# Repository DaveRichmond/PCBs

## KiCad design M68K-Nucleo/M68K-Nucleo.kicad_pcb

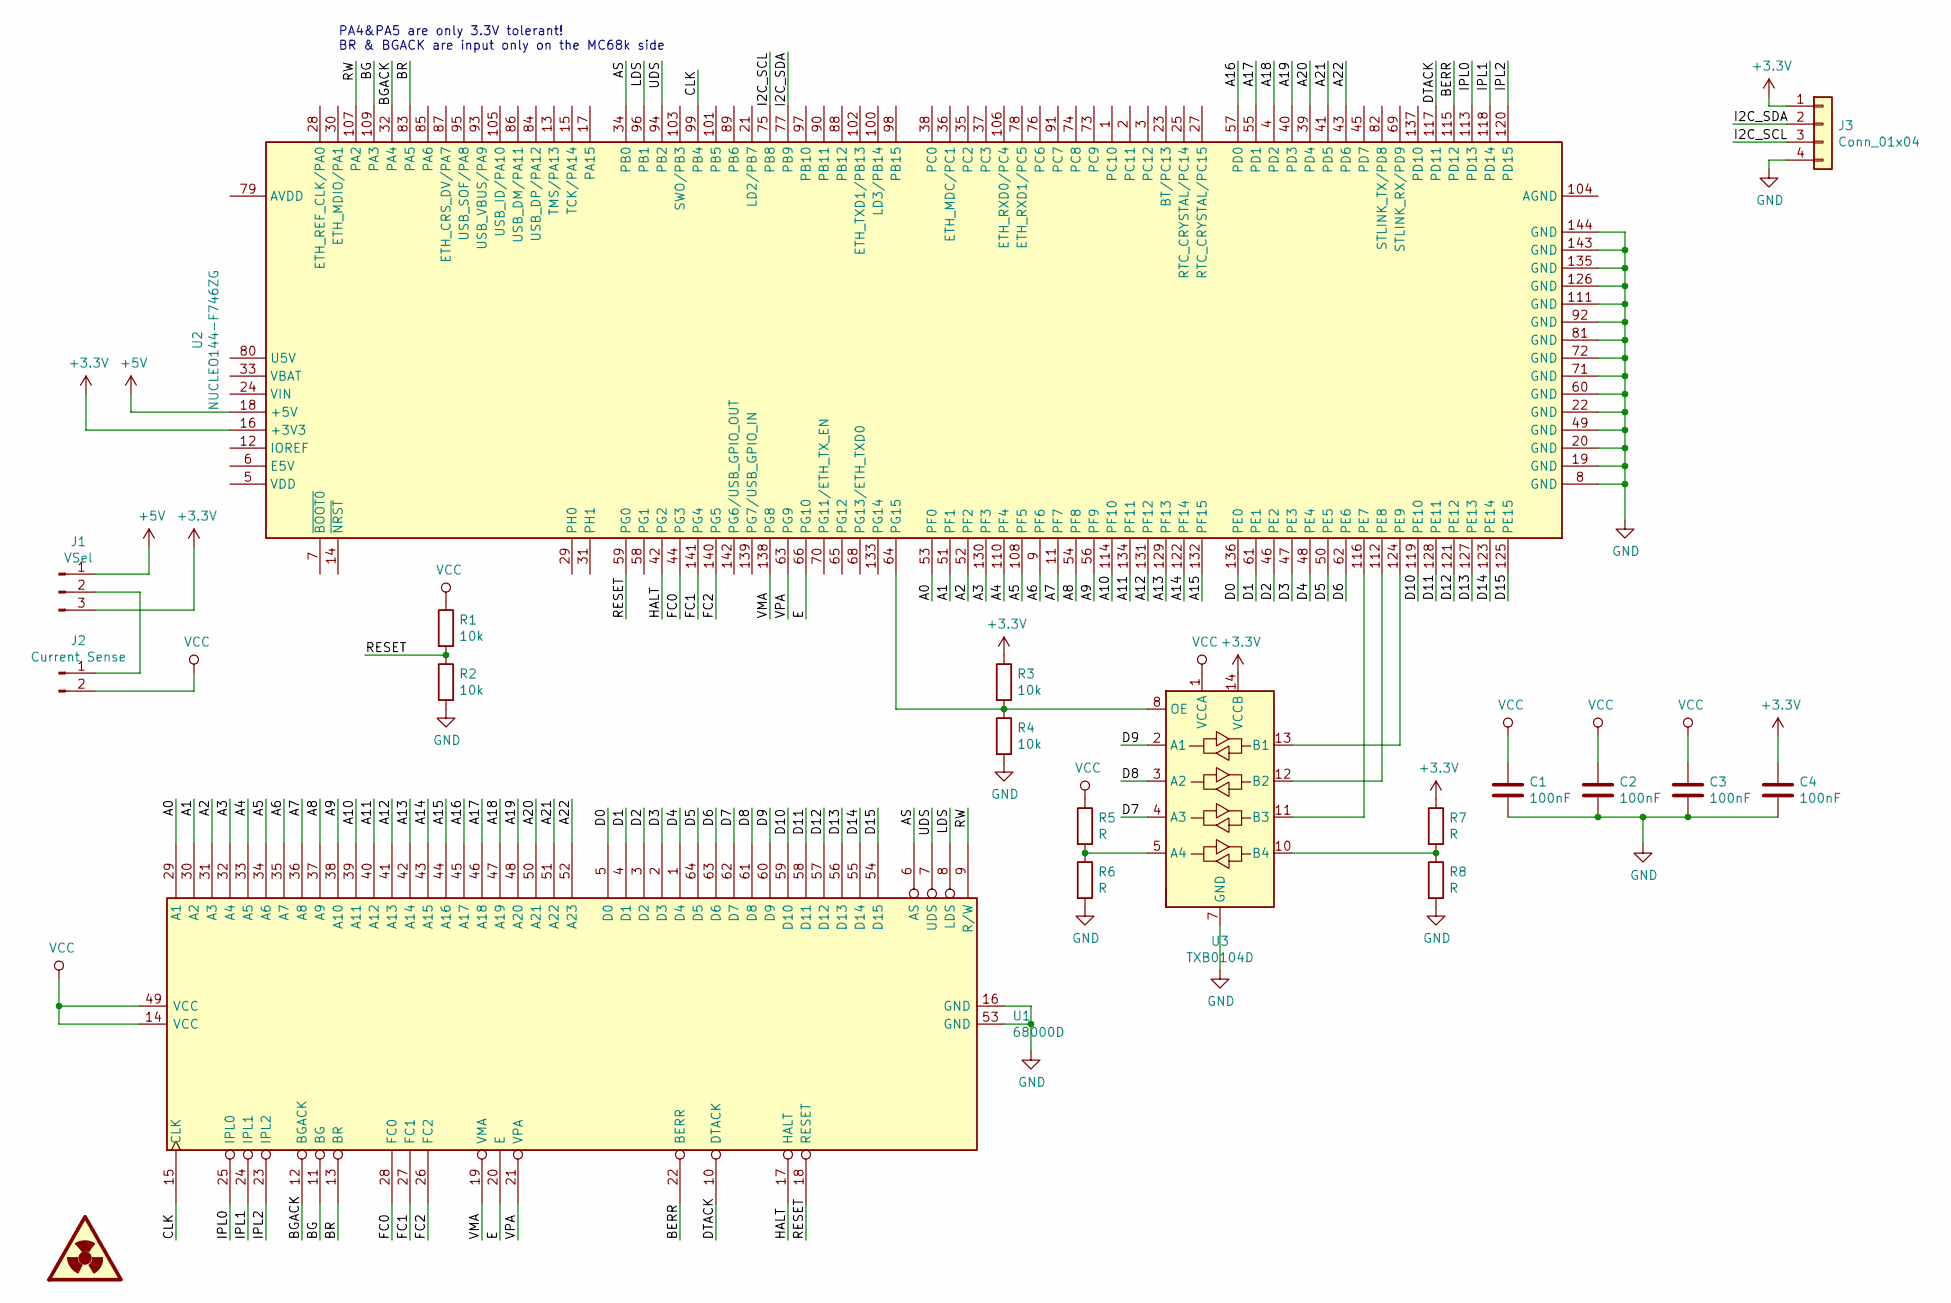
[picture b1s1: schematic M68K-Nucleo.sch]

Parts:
C1, C2, C3, C4: 100nF; C_1206_3216Metric
J1: VSel; PinHeader_1x03_P2.54mm_Vertical
J2: Current Sense; PinHeader_1x02_P2.54mm_Vertical
J3: Conn_01x04; PinHeader_1x04_P2.54mm_Vertical
R1, R2, R3, R4: 10k; R_1206_3216Metric
R5, R6, R7, R8: R; R_1206_3216Metric
U1: 68000D; DIP-64_W22.86mm_Socket_LongPads
U2: NUCLEO144-F746ZG; ST_Morpho_Connector_144_STLink
U3: TXB0104D; TSSOP-14_4.4x5mm_P0.65mm

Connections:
+3V3: C4.1, J1.3, J3.1, R3.1, R7.1, U2.16 (+3V3), U3.14 (VCCB)
+5V: J1.1, U2.18 (+5V)
/A0: U1.29 (A1), U2.53 (PF0)
/A1: U1.30 (A2), U2.51 (PF1)
/A2: U1.31 (A3), U2.52 (PF2)
/A3: U1.32 (A4), U2.130 (PF3)
/A4: U1.33 (A5), U2.110 (PF4)
/A5: U1.34 (A6), U2.108 (PF5)
/A6: U1.35 (A7), U2.9 (PF6)
/A7: U1.36 (A8), U2.11 (PF7)
/A8: U1.37 (A9), U2.54 (PF8)
/A9: U1.38 (A10), U2.56 (PF9)
/A10: U1.39 (A11), U2.114 (PF10)
/A11: U1.40 (A12), U2.134 (PF11)
/A12: U1.41 (A13), U2.131 (PF12)
/A13: U1.42 (A14), U2.129 (PF13)
/A14: U1.43 (A15), U2.122 (PF14)
/A15: U1.44 (A16), U2.132 (PF15)
/A16: U1.45 (A17), U2.57 (PD0)
/A17: U1.46 (A18), U2.55 (PD1)
/A18: U1.47 (A19), U2.4 (PD2)
/A19: U1.48 (A20), U2.40 (PD3)
/A20: U1.50 (A21), U2.39 (PD4)
/A21: U1.51 (A22), U2.41 (PD5)
/A22: U1.52 (A23), U2.43 (PD6)
/AS: U1.6 (AS), U2.34 (PB0)
/BERR: U1.22 (BERR), U2.115 (PD12)
/BG: U1.11 (BG), U2.109 (PA3)
/BGACK: U1.12 (BGACK), U2.32 (PA4)
/BR: U1.13 (BR), U2.83 (PA5)
/CLK: U1.15 (CLK), U2.99 (PB4)
/D0: U1.5 (D0), U2.136 (PE0)
/D1: U1.4 (D1), U2.61 (PE1)
/D2: U1.3 (D2), U2.46 (PE2)
/D3: U1.2 (D3), U2.47 (PE3)
/D4: U1.1 (D4), U2.48 (PE4)
/D5: U1.64 (D5), U2.50 (PE5)
/D6: U1.63 (D6), U2.62 (PE6)
/D7: U1.62 (D7), U3.4 (A3)
/D8: U1.61 (D8), U3.3 (A2)
/D9: U1.60 (D9), U3.2 (A1)
/D10: U1.59 (D10), U2.119 (PE10)
/D11: U1.58 (D11), U2.128 (PE11)
/D12: U1.57 (D12), U2.121 (PE12)
/D13: U1.56 (D13), U2.127 (PE13)
/D14: U1.55 (D14), U2.123 (PE14)
/D15: U1.54 (D15), U2.125 (PE15)
/DTACK: U1.10 (DTACK), U2.117 (PD11)
/E: U1.20 (E), U2.66 (PG10)
/FC0: U1.28 (FC0), U2.44 (PG3)
/FC1: U1.27 (FC1), U2.141 (PG4)
/FC2: U1.26 (FC2), U2.140 (PG5)
/HALT: U1.17 (HALT), U2.42 (PG2)
/I2C_SCL: J3.3, U2.75 (PB8)
/I2C_SDA: J3.2, U2.77 (PB9)
/IPL0: U1.25 (IPL0), U2.113 (PD13)
/IPL1: U1.24 (IPL1), U2.118 (PD14)
/IPL2: U1.23 (IPL2), U2.120 (PD15)
/LDS: U1.8 (LDS), U2.96 (PB1)
/RESET: R1.2, R2.1, U1.18 (RESET), U2.59 (PG0)
/RW: U1.9 (R/W), U2.107 (PA2)
/UDS: U1.7 (UDS), U2.94 (PB2)
/VMA: U1.19 (VMA), U2.138 (PG8)
/VPA: U1.21 (VPA), U2.63 (PG9)
GND: C1.2, C2.2, C3.2, C4.2, J3.4, R2.2, R4.2, R6.2, R8.2, U1.16 (GND), U1.53 (GND), U2.8 (GND), U2.19 (GND), U2.20 (GND), U2.22 (GND), U2.49 (GND), U2.60 (GND), U2.71 (GND), U2.72 (GND), U2.81 (GND), U2.92 (GND), U2.111 (GND), U2.126 (GND), U2.135 (GND), U2.143 (GND), U2.144 (GND), U3.7 (GND)
unnamed: J1.2, J2.1
unnamed: R3.2, R4.1, U2.64 (PG15), U3.8 (OE)
unnamed: R5.2, R6.1, U3.5 (A4)
unnamed: R7.2, R8.1, U3.10 (B4)
unnamed: U2.112 (PE8), U3.12 (B2)
unnamed: U2.116 (PE7), U3.11 (B3)
unnamed: U2.124 (PE9), U3.13 (B1)
VCC: C1.1, C2.1, C3.1, J2.2, R1.1, R5.1, U1.14 (VCC), U1.49 (VCC), U3.1 (VCCA)

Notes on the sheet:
PA4&PA5 are only 3.3V tolerant! BR & BGACK are input only on the MC68k side

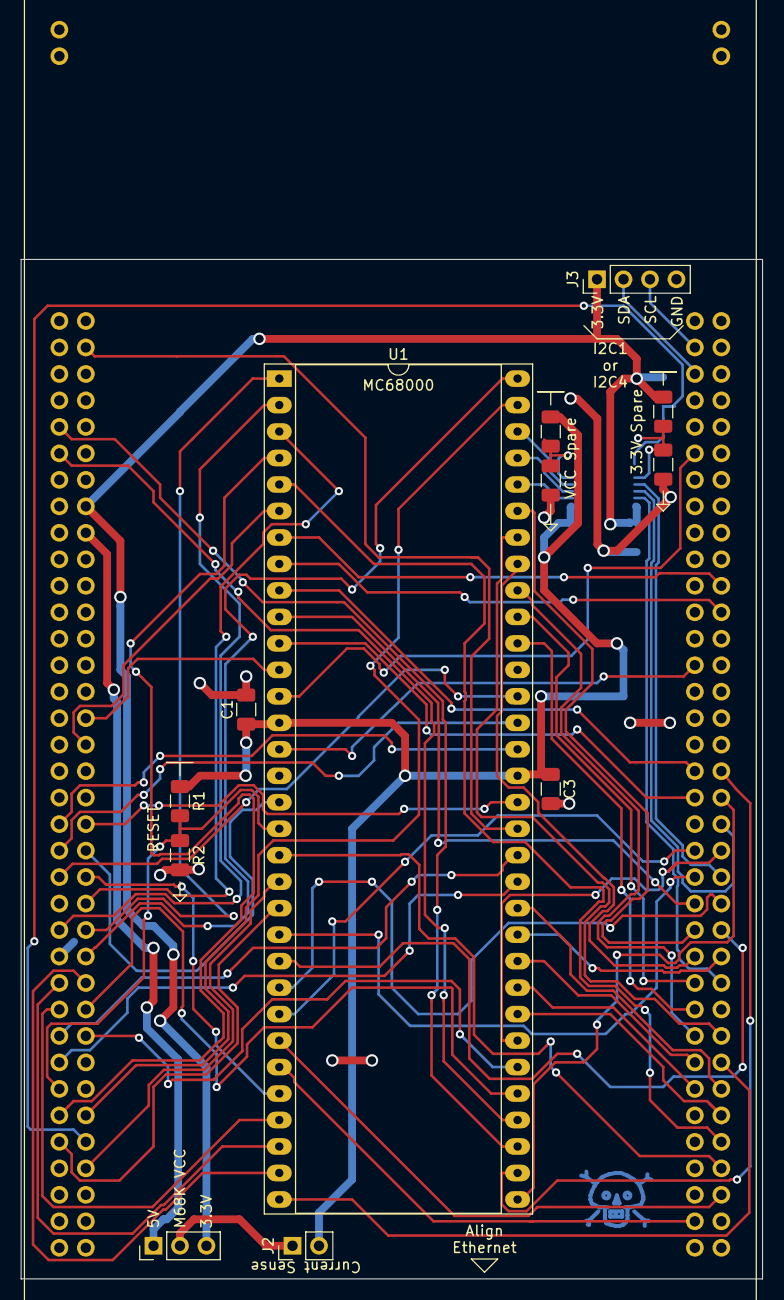
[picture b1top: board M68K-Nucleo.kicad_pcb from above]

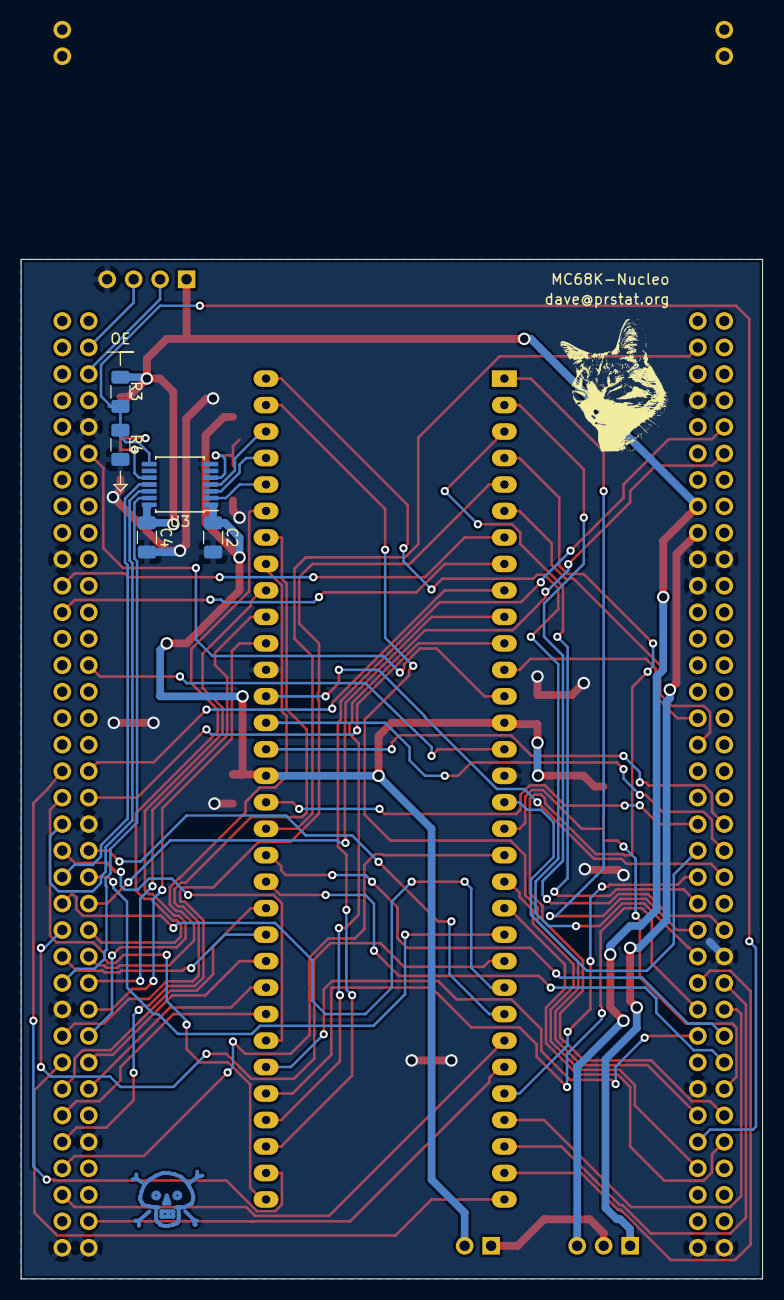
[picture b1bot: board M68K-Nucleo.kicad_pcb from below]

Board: 2 copper layers, 71.1 x 97.8 mm, 18 parts (5 on the bottom side), 73 nets.

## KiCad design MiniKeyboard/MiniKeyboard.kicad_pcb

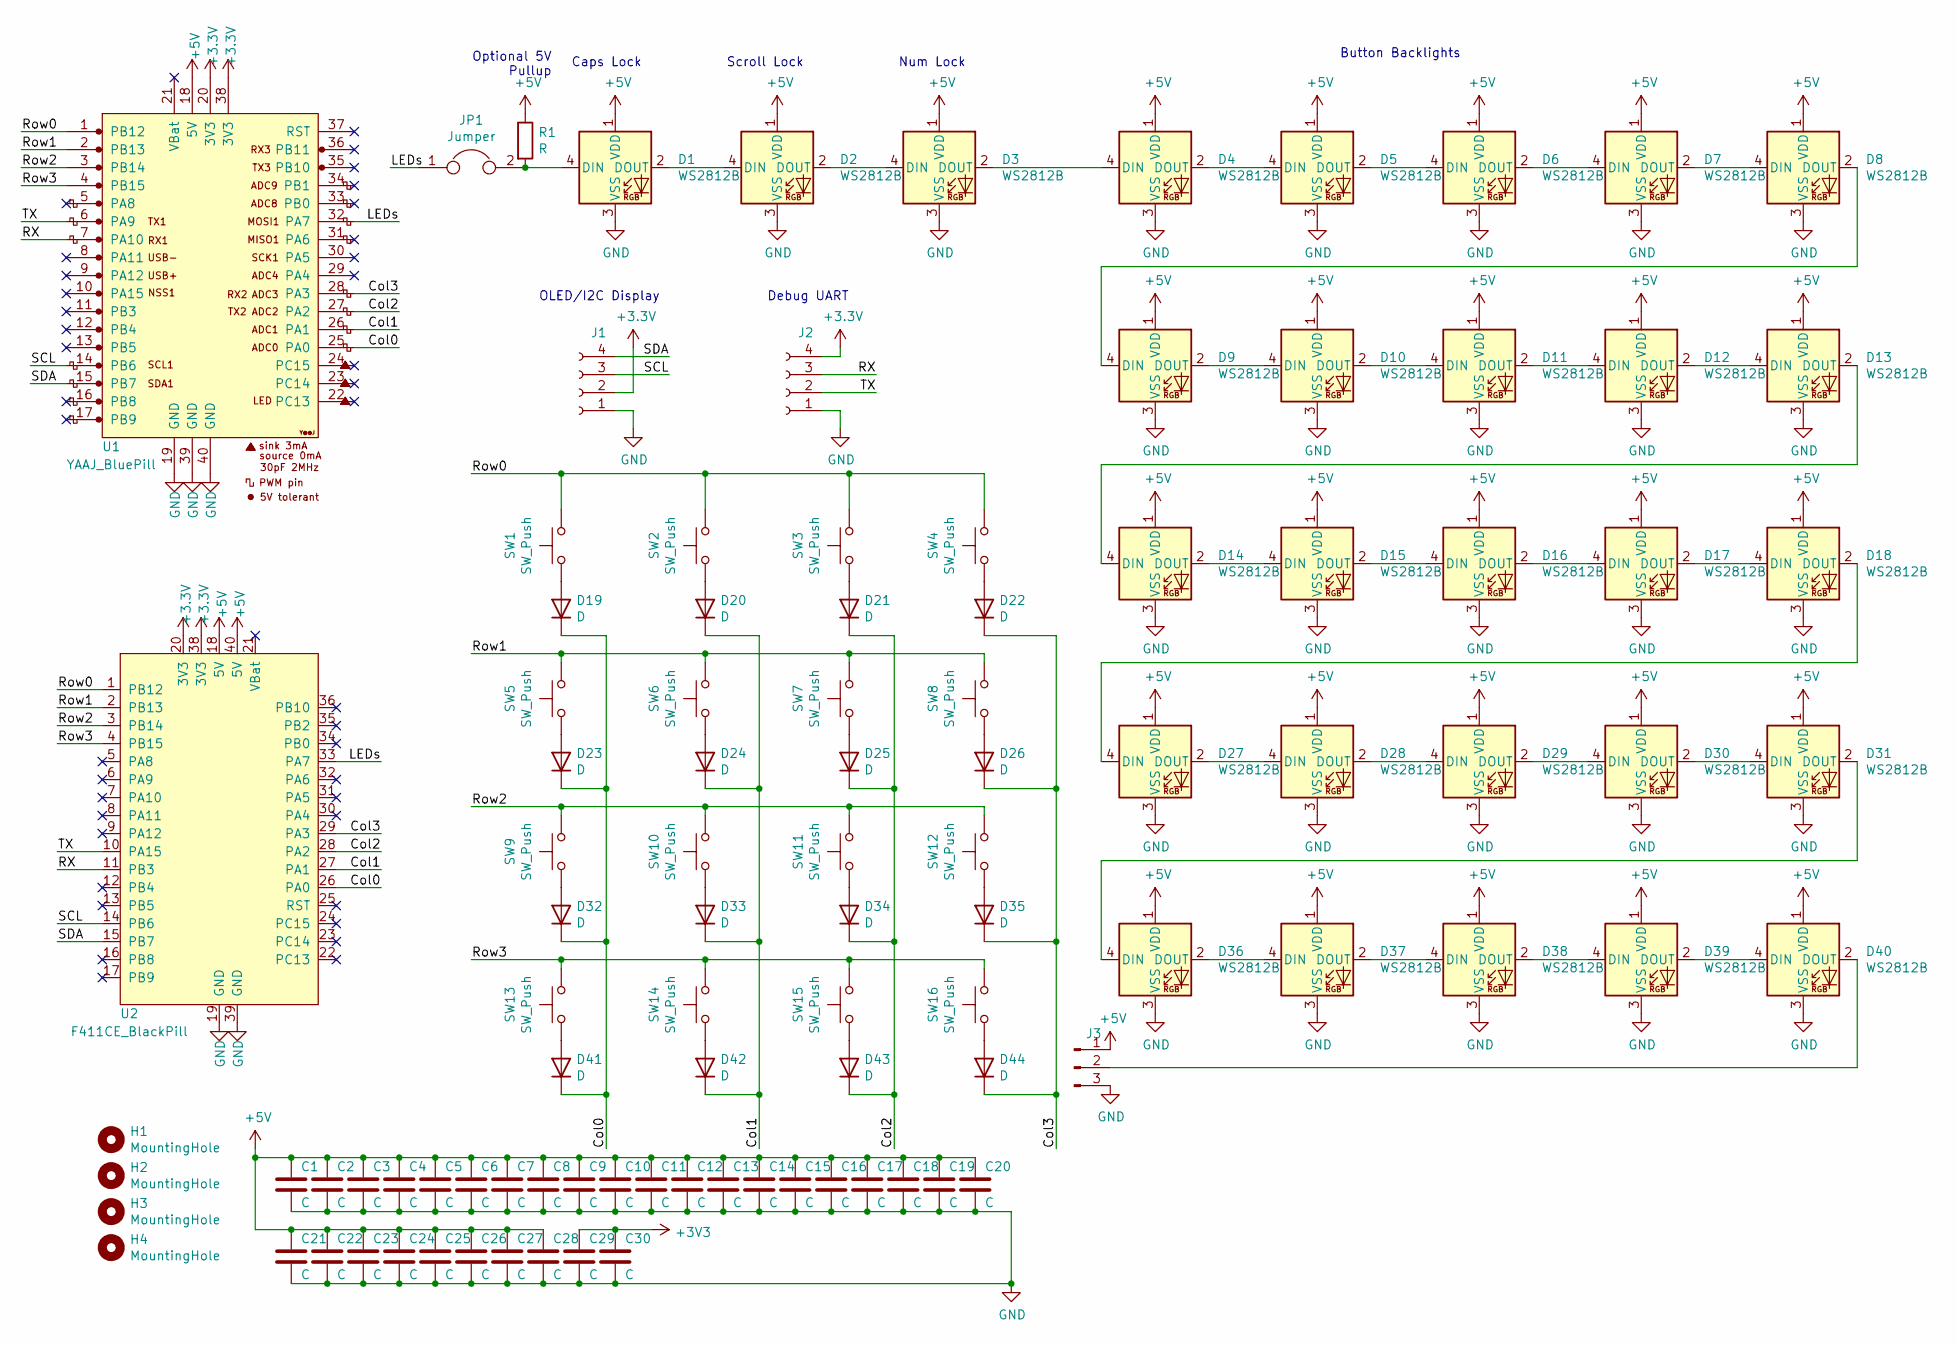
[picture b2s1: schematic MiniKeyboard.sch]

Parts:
C1, C2, C3, C4, C5, C6, C7, C8, C9, C10, C11, C12, C13, C14, C15, C16, C17, C18, C19, C20, C21, C22, C23, C24, C25, C26, C27, C28, C29, C30: C; C_0805_2012Metric_Pad1.18x1.45mm_HandSolder
D1, D2, D3, D4, D5, D6, D7, D8, D9, D10, D11, D12, D13, D14, D15, D16, D17, D18, D27, D28, D29, D30, D31, D36, D37, D38, D39, D40: WS2812B; LED_WS2812B_PLCC4_5.0x5.0mm_P3.2mm
D19, D20, D21, D22, D23, D24, D25, D26, D32, D33, D34, D35, D41, D42, D43, D44: D; D_SOT-23_ANK
H1, H2, H3, H4: MountingHole; MountingHole_5mm
J1, J2: Conn_01x04_Female; PinSocket_1x04_P2.54mm_Vertical
J3: Conn_01x03_Male; PinSocket_1x03_P2.54mm_Vertical
JP1: Jumper; SolderJumper-2_P1.3mm_Bridged_RoundedPad1.0x1.5mm
R1: R; R_1206_3216Metric_Pad1.30x1.75mm_HandSolder
SW1, SW2, SW3, SW4, SW5, SW6, SW7, SW8, SW9, SW10, SW11, SW12, SW13, SW14, SW15, SW16: SW_Push; SW_Cherry_MX_1.00u_PCB
U1: YAAJ_BluePill; YAAJ_BluePill_2
U2: F411CE_BlackPill; F411CE-Blackpill

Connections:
+5V: C1.1, C2.1, C3.1, C4.1, C5.1, C6.1, C7.1, C8.1, C9.1, C10.1, C11.1, C12.1, C13.1, C14.1, C15.1, C16.1, C17.1, C18.1, C19.1, C20.1, C21.1, C22.1, C23.1, C24.1, C25.1, C26.1, C27.1, C28.1, D1.1 (VDD), D2.1 (VDD), D3.1 (VDD), D4.1 (VDD), D5.1 (VDD), D6.1 (VDD), D7.1 (VDD), D8.1 (VDD), D9.1 (VDD), D10.1 (VDD), D11.1 (VDD), D12.1 (VDD), D13.1 (VDD), D14.1 (VDD), D15.1 (VDD), D16.1 (VDD), D17.1 (VDD), D18.1 (VDD), D27.1 (VDD), D28.1 (VDD), D29.1 (VDD), D30.1 (VDD), D31.1 (VDD), D36.1 (VDD), D37.1 (VDD), D38.1 (VDD), D39.1 (VDD), D40.1 (VDD), J3.1, R1.1, U1.18 (5V), U2.18 (5V), U2.40 (5V)
/Col0: D19.1 (K), D23.1 (K), D32.1 (K), D41.1 (K), U1.25 (PA0), U2.26 (PA0)
/Col1: D20.1 (K), D24.1 (K), D33.1 (K), D42.1 (K), U1.26 (PA1), U2.27 (PA1)
/Col2: D21.1 (K), D25.1 (K), D34.1 (K), D43.1 (K), U1.27 (PA2), U2.28 (PA2)
/Col3: D22.1 (K), D26.1 (K), D35.1 (K), D44.1 (K), U1.28 (PA3), U2.29 (PA3)
/LEDs: JP1.1, U1.32 (PA7), U2.33 (PA7)
/RX: J2.3, U1.7 (PA10), U2.11 (PB3)
/Row0: SW1.2, SW2.2, SW3.2, SW4.2, U1.1 (PB12), U2.1 (PB12)
/Row1: SW5.2, SW6.2, SW7.2, SW8.2, U1.2 (PB13), U2.2 (PB13)
/Row2: SW9.2, SW10.2, SW11.2, SW12.2, U1.3 (PB14), U2.3 (PB14)
/Row3: SW13.2, SW14.2, SW15.2, SW16.2, U1.4 (PB15), U2.4 (PB15)
/SCL: J1.3, U1.14 (PB6), U2.14 (PB6)
/SDA: J1.4, U1.15 (PB7), U2.15 (PB7)
/TX: J2.2, U1.6 (PA9), U2.10 (PA15)
GND: C1.2, C2.2, C3.2, C4.2, C5.2, C6.2, C7.2, C8.2, C9.2, C10.2, C11.2, C12.2, C13.2, C14.2, C15.2, C16.2, C17.2, C18.2, C19.2, C20.2, C21.2, C22.2, C23.2, C24.2, C25.2, C26.2, C27.2, C28.2, C29.2, C30.2, D1.3 (VSS), D2.3 (VSS), D3.3 (VSS), D4.3 (VSS), D5.3 (VSS), D6.3 (VSS), D7.3 (VSS), D8.3 (VSS), D9.3 (VSS), D10.3 (VSS), D11.3 (VSS), D12.3 (VSS), D13.3 (VSS), D14.3 (VSS), D15.3 (VSS), D16.3 (VSS), D17.3 (VSS), D18.3 (VSS), D27.3 (VSS), D28.3 (VSS), D29.3 (VSS), D30.3 (VSS), D31.3 (VSS), D36.3 (VSS), D37.3 (VSS), D38.3 (VSS), D39.3 (VSS), D40.3 (VSS), J1.1, J2.1, J3.3, U1.19 (GND), U1.39 (GND), U1.40 (GND), U2.19 (GND), U2.39 (GND)
unnamed: D1.2 (DOUT), D2.4 (DIN)
unnamed: D1.4 (DIN), JP1.2, R1.2
unnamed: D2.2 (DOUT), D3.4 (DIN)
unnamed: D3.2 (DOUT), D4.4 (DIN)
unnamed: D4.2 (DOUT), D5.4 (DIN)
unnamed: D5.2 (DOUT), D6.4 (DIN)
unnamed: D6.2 (DOUT), D7.4 (DIN)
unnamed: D7.2 (DOUT), D8.4 (DIN)
unnamed: D8.2 (DOUT), D9.4 (DIN)
unnamed: D10.2 (DOUT), D11.4 (DIN)
unnamed: D9.2 (DOUT), D10.4 (DIN)
unnamed: D11.2 (DOUT), D12.4 (DIN)
unnamed: D12.2 (DOUT), D13.4 (DIN)
unnamed: D13.2 (DOUT), D14.4 (DIN)
unnamed: D14.2 (DOUT), D15.4 (DIN)
unnamed: D15.2 (DOUT), D16.4 (DIN)
unnamed: D16.2 (DOUT), D17.4 (DIN)
unnamed: D17.2 (DOUT), D18.4 (DIN)
unnamed: D18.2 (DOUT), D27.4 (DIN)
unnamed: D19.2 (A), SW1.1
unnamed: D20.2 (A), SW2.1
unnamed: D21.2 (A), SW3.1
unnamed: D22.2 (A), SW4.1
unnamed: D23.2 (A), SW5.1
unnamed: D24.2 (A), SW6.1
unnamed: D25.2 (A), SW7.1
unnamed: D26.2 (A), SW8.1
unnamed: D27.2 (DOUT), D28.4 (DIN)
unnamed: D28.2 (DOUT), D29.4 (DIN)
unnamed: D29.2 (DOUT), D30.4 (DIN)
unnamed: D30.2 (DOUT), D31.4 (DIN)
unnamed: D31.2 (DOUT), D36.4 (DIN)
unnamed: D32.2 (A), SW9.1
unnamed: D33.2 (A), SW10.1
unnamed: D34.2 (A), SW11.1
unnamed: D35.2 (A), SW12.1
unnamed: D36.2 (DOUT), D37.4 (DIN)
unnamed: D37.2 (DOUT), D38.4 (DIN)
unnamed: D38.2 (DOUT), D39.4 (DIN)
unnamed: D39.2 (DOUT), D40.4 (DIN)
unnamed: D40.2 (DOUT), J3.2
unnamed: D41.2 (A), SW13.1
unnamed: D42.2 (A), SW14.1
unnamed: D43.2 (A), SW15.1
unnamed: D44.2 (A), SW16.1

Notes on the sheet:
OLED/I2C Display
Debug UART
Caps Lock
Scroll Lock
Num Lock
Button Backlights
Optional 5V Pullup

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
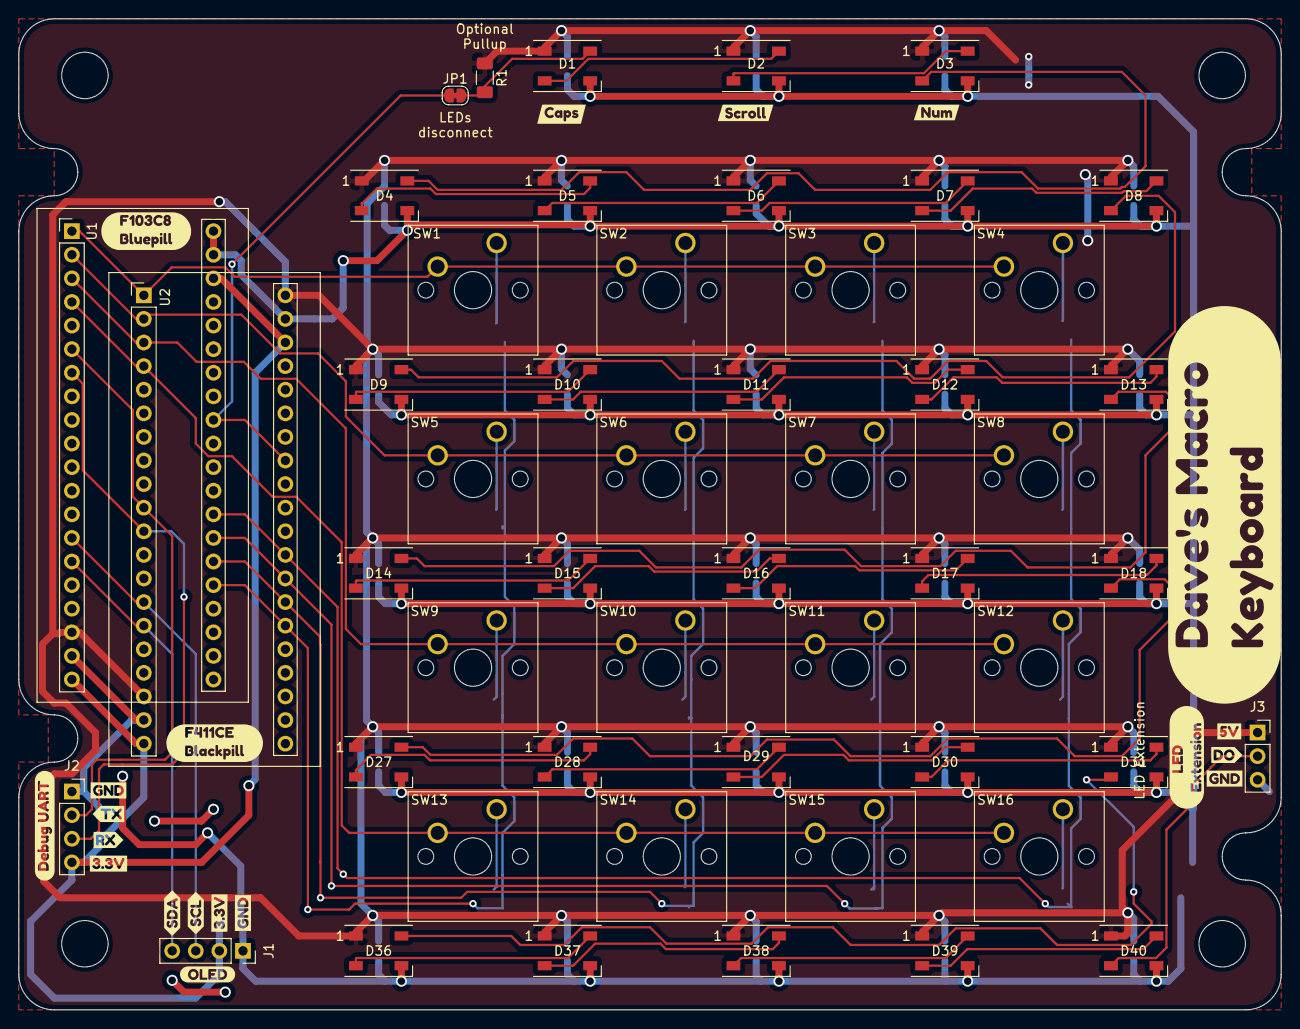
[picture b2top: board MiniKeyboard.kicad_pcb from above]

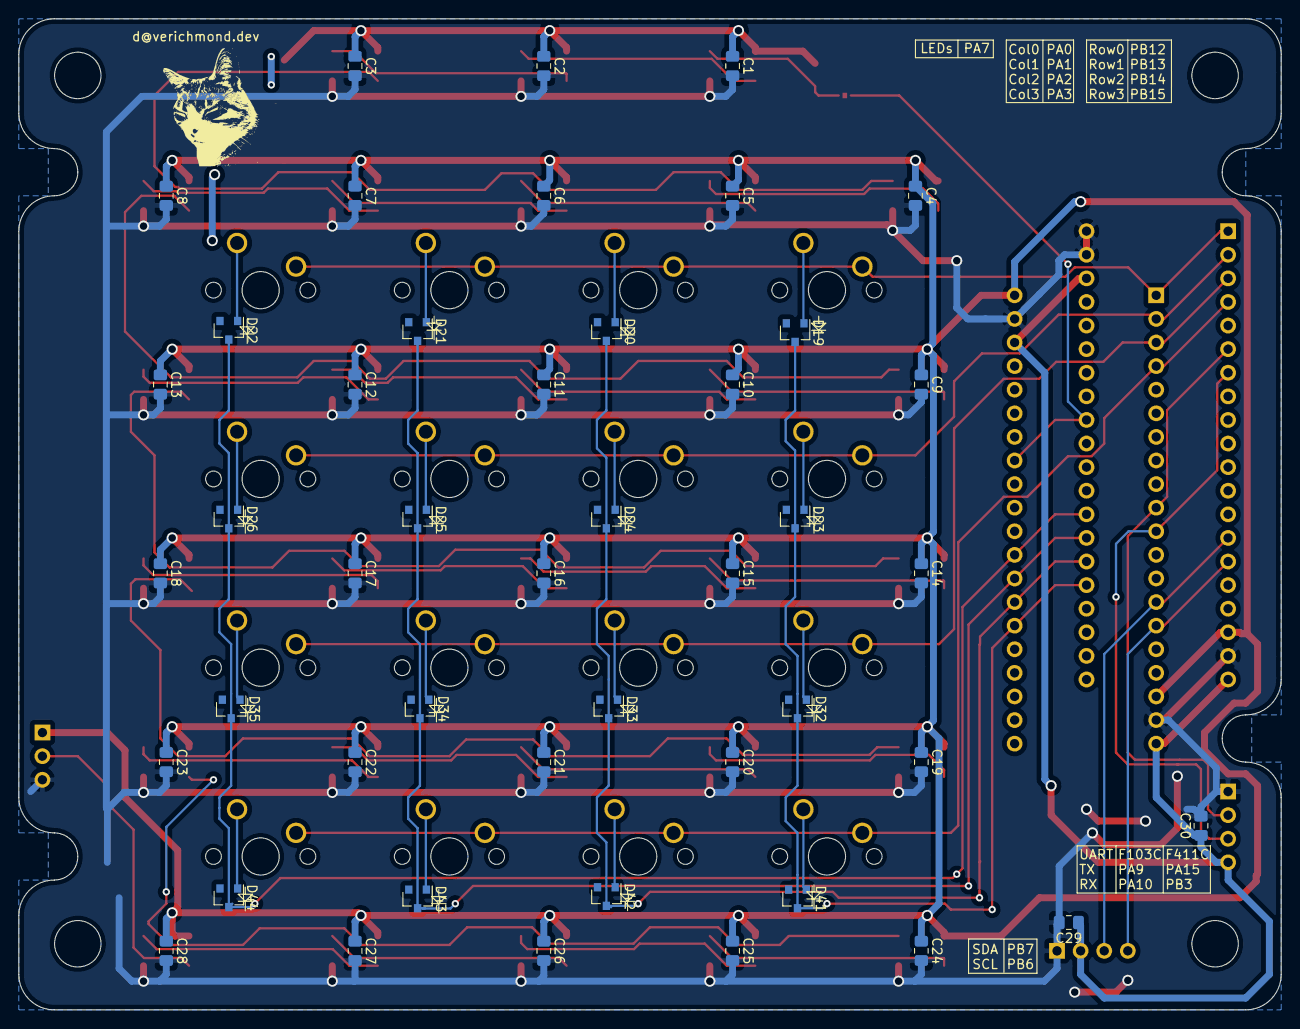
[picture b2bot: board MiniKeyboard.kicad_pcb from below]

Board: 2 copper layers, 135.9 x 106.7 mm, 121 parts (46 on the bottom side), 61 nets.

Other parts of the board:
svg2mod, svg2mod#2, svg2mod#3, svg2mod#4, svg2mod#5, svg2mod#6, svg2mod#7, svg2mod#8, svg2mod#9, svg2mod#10, svg2mod#11, svg2mod#12, svg2mod#13, svg2mod#14, svg2mod#15, svg2mod#16, svg2mod#17, svg2mod#18, svg2mod#19, svg2mod#20: G***; label

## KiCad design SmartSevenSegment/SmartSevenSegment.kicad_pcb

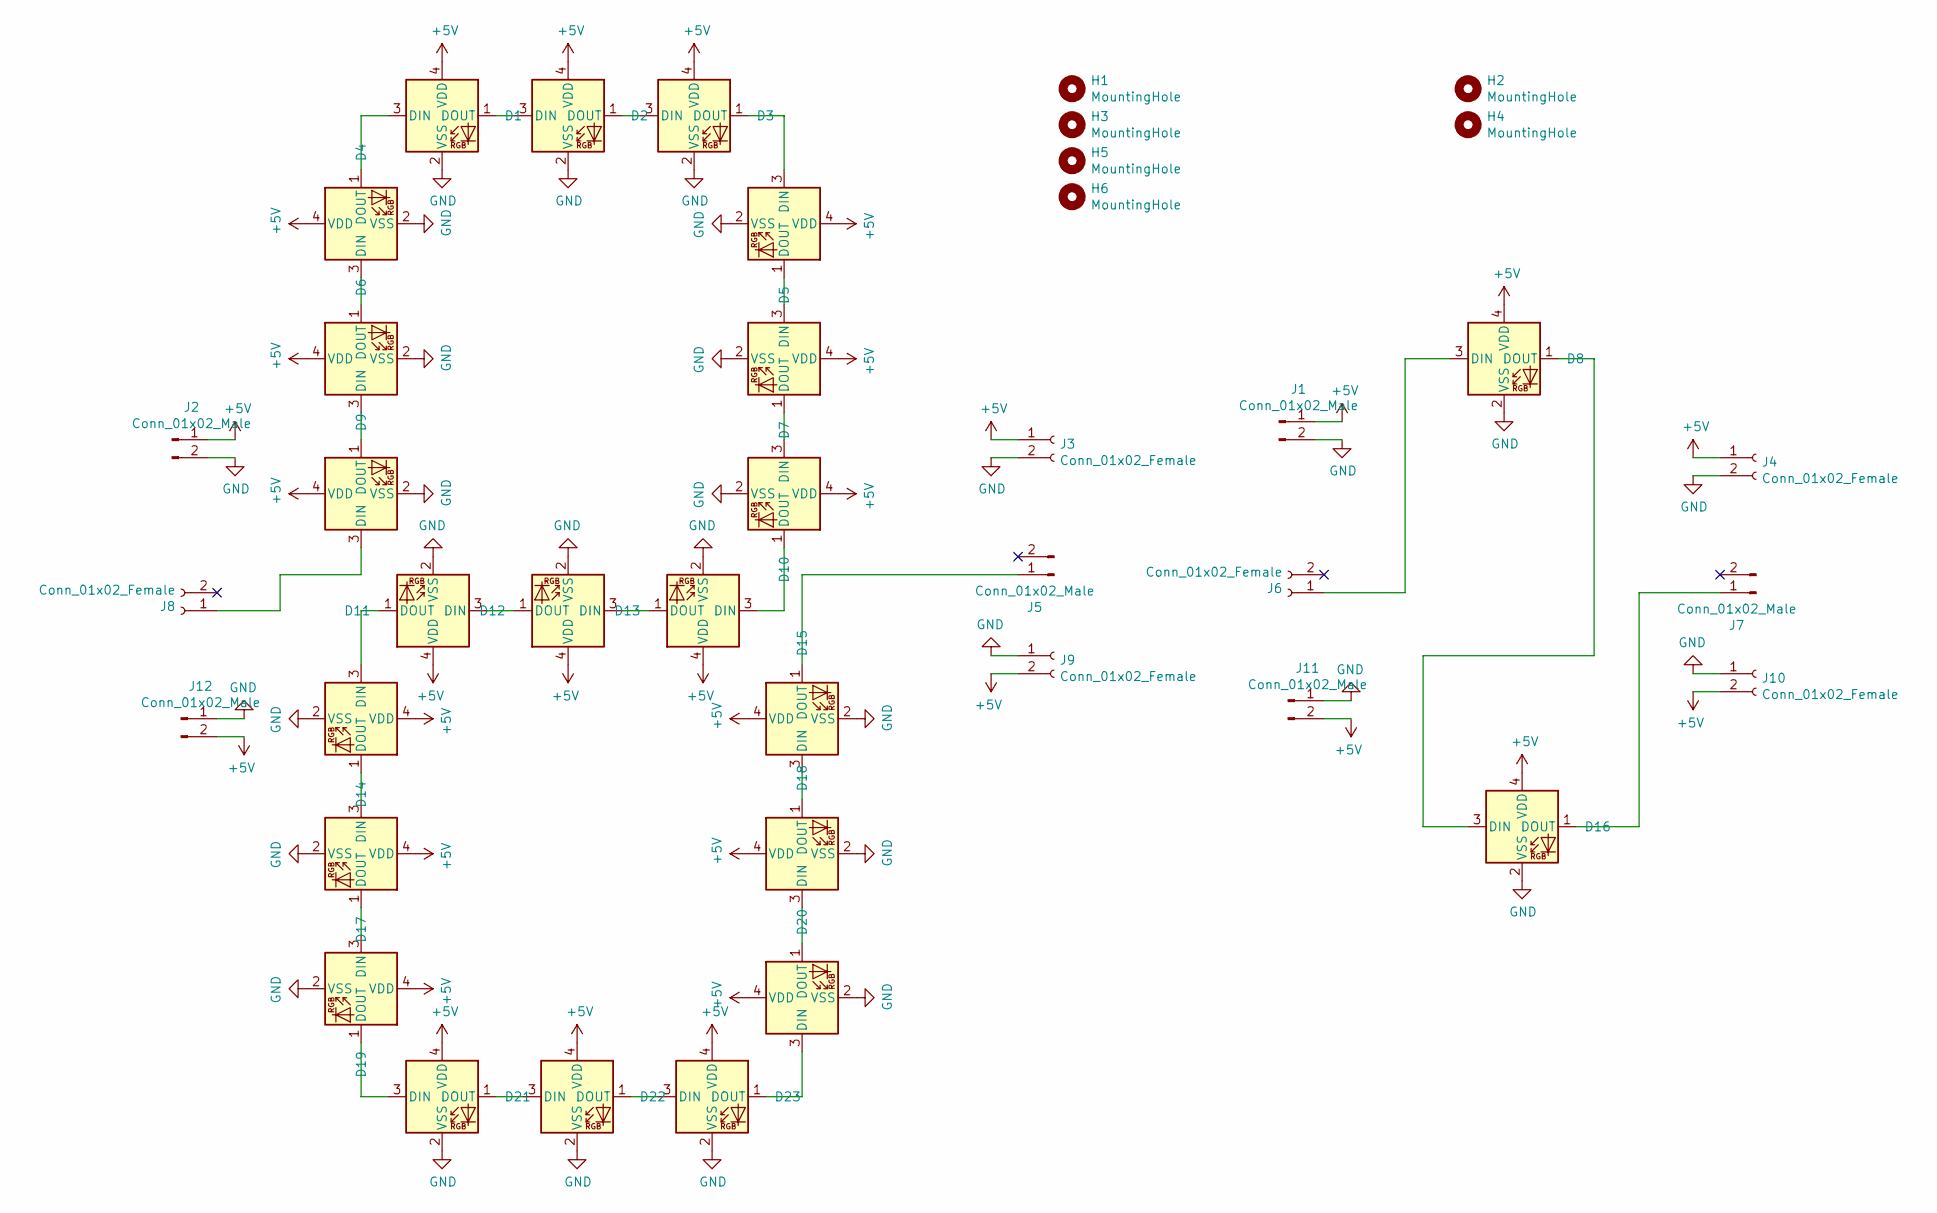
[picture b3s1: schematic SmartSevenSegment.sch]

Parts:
D1, D2, D3, D4, D5, D6, D7, D8, D9, D10, D11, D12, D13, D14, D15, D16, D17, D18, D19, D20, D21, D22, D23: SK6812MINI; LED_SK6812MINI_PLCC4_3.5x3.5mm_P1.75mm
H1, H2, H3, H4, H5, H6: MountingHole; MountingHole_2.1mm
J1, J2, J5, J7, J11, J12: Conn_01x02_Male; PinHeader_1x02_P2.54mm_Vertical
J3, J4, J6, J8, J9, J10: Conn_01x02_Female; PinSocket_1x02_P2.54mm_Vertical

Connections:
+5V: D1.4 (VDD), D2.4 (VDD), D3.4 (VDD), D4.4 (VDD), D5.4 (VDD), D6.4 (VDD), D7.4 (VDD), D8.4 (VDD), D9.4 (VDD), D10.4 (VDD), D11.4 (VDD), D12.4 (VDD), D13.4 (VDD), D14.4 (VDD), D15.4 (VDD), D16.4 (VDD), D17.4 (VDD), D18.4 (VDD), D19.4 (VDD), D20.4 (VDD), D21.4 (VDD), D22.4 (VDD), D23.4 (VDD), J1.1, J2.1, J3.1, J4.1, J9.2, J10.2, J11.2, J12.2
GND: D1.2 (VSS), D2.2 (VSS), D3.2 (VSS), D4.2 (VSS), D5.2 (VSS), D6.2 (VSS), D7.2 (VSS), D8.2 (VSS), D9.2 (VSS), D10.2 (VSS), D11.2 (VSS), D12.2 (VSS), D13.2 (VSS), D14.2 (VSS), D15.2 (VSS), D16.2 (VSS), D17.2 (VSS), D18.2 (VSS), D19.2 (VSS), D20.2 (VSS), D21.2 (VSS), D22.2 (VSS), D23.2 (VSS), J1.2, J2.2, J3.2, J4.2, J9.1, J10.1, J11.1, J12.1
unnamed: D1.1 (DOUT), D2.3 (DIN)
unnamed: D1.3 (DIN), D4.1 (DOUT)
unnamed: D2.1 (DOUT), D3.3 (DIN)
unnamed: D3.1 (DOUT), D5.3 (DIN)
unnamed: D4.3 (DIN), D6.1 (DOUT)
unnamed: D5.1 (DOUT), D7.3 (DIN)
unnamed: D6.3 (DIN), D9.1 (DOUT)
unnamed: D8.3 (DIN), J6.1
unnamed: D9.3 (DIN), J8.1
unnamed: D10.1 (DOUT), D13.3 (DIN)
unnamed: D7.1 (DOUT), D10.3 (DIN)
unnamed: D11.1 (DOUT), D14.3 (DIN)
unnamed: D11.3 (DIN), D12.1 (DOUT)
unnamed: D12.3 (DIN), D13.1 (DOUT)
unnamed: D14.1 (DOUT), D17.3 (DIN)
unnamed: D15.1 (DOUT), J5.1
unnamed: D15.3 (DIN), D18.1 (DOUT)
unnamed: D16.1 (DOUT), J7.1
unnamed: D8.1 (DOUT), D16.3 (DIN)
unnamed: D17.1 (DOUT), D19.3 (DIN)
unnamed: D18.3 (DIN), D20.1 (DOUT)
unnamed: D19.1 (DOUT), D21.3 (DIN)
unnamed: D20.3 (DIN), D23.1 (DOUT)
unnamed: D21.1 (DOUT), D22.3 (DIN)
unnamed: D22.1 (DOUT), D23.3 (DIN)

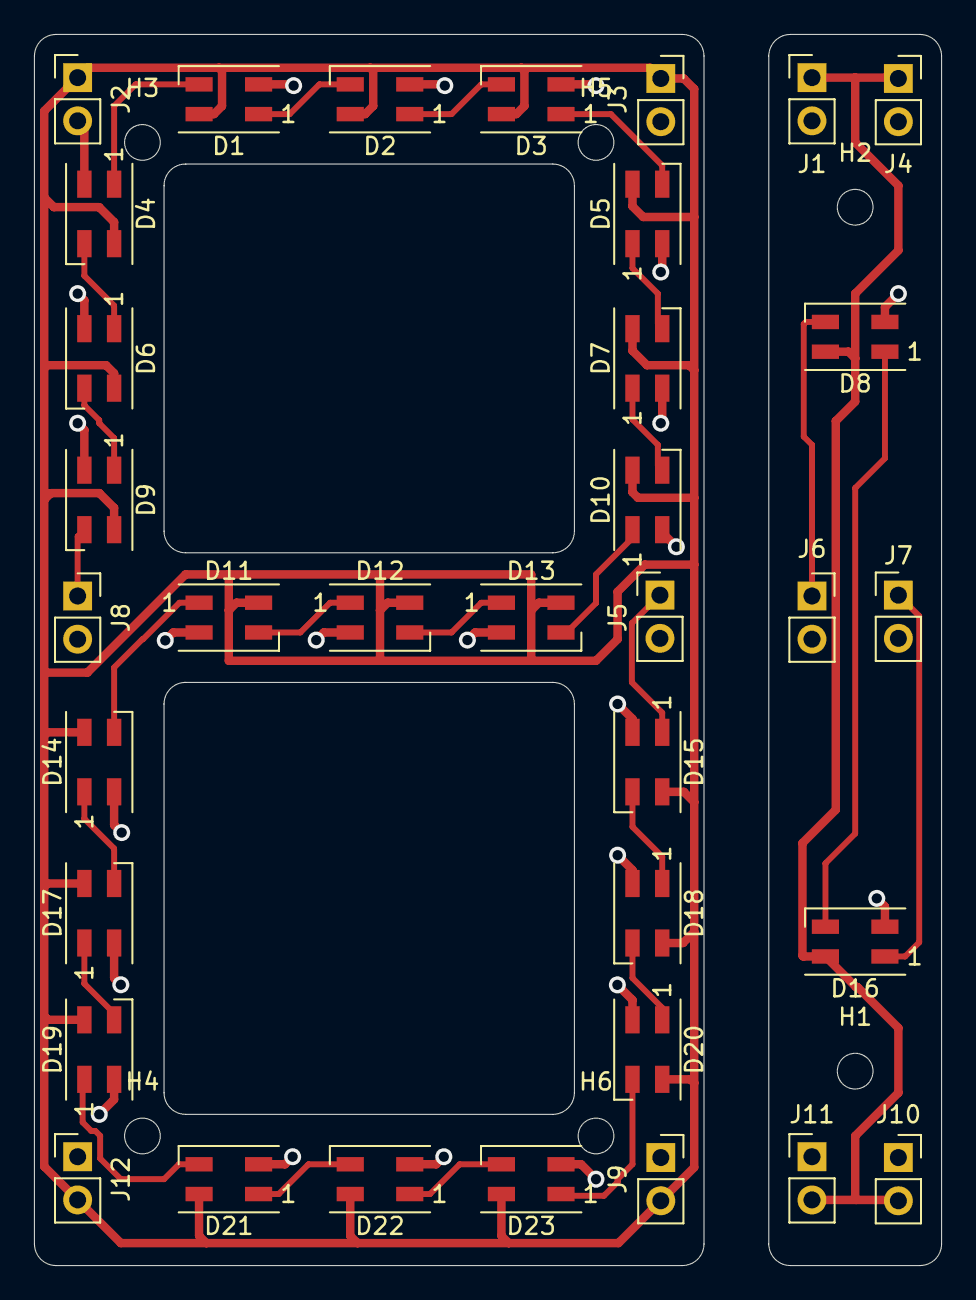
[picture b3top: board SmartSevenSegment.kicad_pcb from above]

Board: 2 copper layers, 53.3 x 72.4 mm, 41 parts (0 on the bottom side), 27 nets.

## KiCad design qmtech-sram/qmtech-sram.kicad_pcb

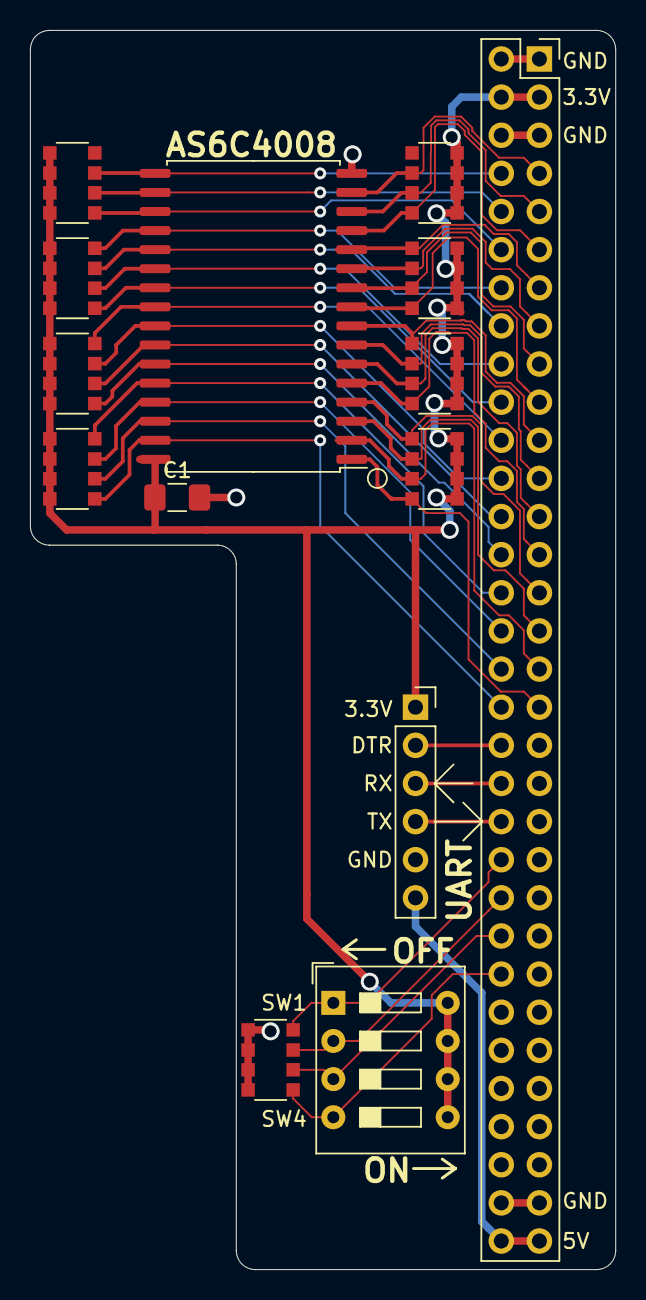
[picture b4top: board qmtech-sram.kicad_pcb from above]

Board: 2 copper layers, 39.0 x 82.5 mm, 14 parts (0 on the bottom side), 40 nets.

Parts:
C1: C; C_1206_3216Metric_Pad1.42x1.75mm_HandSolder
J1: Conn_02x32_Odd_Even; PinSocket_2x32_P2.54mm_Vertical
J2: Conn_01x06; PinSocket_1x06_P2.54mm_Vertical
RN1, RN2, RN3, RN4, RN5, RN6, RN7, RN8, RN9: R_Pack04; R_Array_Convex_4x1206
SW1: SW_DIP_x04; SW_DIP_SPSTx04_Slide_9.78x12.34mm_W7.62mm_P2.54mm
U1: AS6C4008-55PCN; SSOP-32_11.305x20.495mm_P1.27mm

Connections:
+3V3: C1.1, J1.3, J1.4, J2.1, RN1.5, RN1.6, RN1.7, RN1.8, RN2.5, RN2.6, RN2.7, RN2.8, RN3.5, RN3.6, RN3.7, RN3.8, RN4.1, RN4.2, RN4.3, RN4.4, RN5.1, RN5.2, RN5.3, RN5.4, RN6.5, RN6.6, RN6.7, RN6.8, RN7.1, RN7.2, RN7.3, RN7.4, RN8.1, RN8.2, RN8.3, RN8.4, SW1.5, SW1.6, SW1.7, SW1.8, U1.32
+5V: J1.63, J1.64, J2.6
/A0: J1.13, RN1.1, U1.12
/A1: J1.15, RN1.2, U1.11
/A2: J1.17, RN1.3, U1.10
/A3: J1.19, RN1.4, U1.9
/A4: J1.21, RN3.1, U1.8
/A5: J1.23, RN3.2, U1.7
/A6: J1.25, RN3.3, U1.6
/A7: J1.27, RN3.4, U1.5
/A8: J1.28, RN2.1, U1.27
/A9: J1.26, RN2.2, U1.26
/A10: J1.20, RN8.5, U1.23
/A11: J1.24, RN2.3, U1.25
/A12: J1.29, RN6.1, U1.4
/A13: J1.30, RN4.8, U1.28
/A14: J1.31, RN6.2, U1.3
/A15: J1.36, RN4.5, U1.31
/A16: J1.33, RN6.3, U1.2
/A17: J1.34, RN4.6, U1.30
/A18: J1.35, RN6.4, U1.1
/CE: J1.18, RN8.6, U1.22
/DQ0: J1.11, RN5.8, U1.13
/DQ1: J1.9, RN5.7, U1.14
/DQ2: J1.7, RN5.6, U1.15
/DQ3: J1.8, RN7.7, U1.17
/DQ4: J1.10, RN7.6, U1.18
/DQ5: J1.12, RN7.5, U1.19
/DQ6: J1.14, RN8.8, U1.20
/DQ7: J1.16, RN8.7, U1.21
/DTR: J1.38, J2.2
/OE: J1.22, RN2.4, U1.24
/RX: J1.40, J2.3
/SW1: J1.44, RN9.8, SW1.1
/SW2: J1.46, RN9.7, SW1.2
/SW3: J1.48, RN9.6, SW1.3
/SW4: J1.50, RN9.5, SW1.4
/TX: J1.42, J2.4
/WE: J1.32, RN4.7, U1.29
GND: C1.2, J1.1, J1.2, J1.5, J1.6, J1.61, J1.62, J2.5, RN9.1, RN9.2, RN9.3, RN9.4, U1.16
